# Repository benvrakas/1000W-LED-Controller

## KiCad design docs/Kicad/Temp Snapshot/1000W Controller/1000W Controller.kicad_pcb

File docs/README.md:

# 1000W LED Projector Controller Firmware (v2.0)

Firmware for a high-power (1000W) LED projector controller based on the **Adafruit Feather M4 CAN Express (SAME51)**. It manages a **Mean Well UHP-1500-48** power supply via CAN Bus, controls active liquid cooling, and provides a user interface via a Button, OLED, and Rotary Encoder.

## 1. System Overview
This system manages the power and cooling of a high-power COB LED array. It ensures safe operation through rigorous state management, PI-based thermal monitoring, and active fault protection.

### Key Features
*   **Power Control**: Digital control of **Mean Well UHP-1500-48** PSU via Native CAN Bus (PMBus protocol). Includes programmable output voltage (50~120%) and constant current limits (20~100%).
*   **Active Cooling**: PI (Proportional-Integral) controllers dynamically adjust Radiator Fans, Pump, and Aux Fans to strictly maintain target temperatures.
*   **User Interface**: OLED status display (128x32) and Rotary Encoder input for brightness mapping.
*   **Safety**:
    *   Latched `ERROR_KILL` state for critical faults (Over-temp, Pump failure, CAN timeout).
    *   Hardware enable lines dropped immediately on fault.

## 2. Hardware Components
The system manages the following specific high-performance components:
*   **Microcontroller:** Adafruit Feather M4 CAN Express (SAME51J19A).
*   **LED Array:** **Getian High-Density COB LED**. These specialized emitters produce intense localized heat and require precise power limits (up to 22.0A) and strict thermal management to prevent lumen degradation.
*   **Power Supply:** **Mean Well UHP-1500-48**. A 1500W, 48V industrial power supply. It is controlled via the PMBus protocol over the native CAN bus, allowing the microcontroller to set exact current limits and slew rates digitally.
*   **Cooling System (Liquid Loop):**
    *   **Water Pump:** **Xylem/Laing Ecocirc D5 Vario**. A highly reliable, shaftless spherical motor pump controlled via PWM with tachometer feedback.
    *   **Radiator Fans:** High static pressure 120mm PWM fans (e.g., NMB Technologies 12038VA series) to force air through the liquid cooling radiator.
    *   **Auxiliary/Lens Fans:** Additional PWM fans (e.g., Delta FFB series) to cool the optical path and projector lenses.
*   **Sensors:** Two 10k NTC Thermistors (Beta: 3950) for monitoring both the LED block temperature and the circulating Water temperature.

### 2.1 Pinout Mapping

## 3. Core Architectural Pattern
The software is structured using a **Dependency Injection (DI)** pattern, implemented in C++ with the Arduino/PlatformIO framework. This cleanly separates the hardware driver layer from the higher-level business logic.

### 3.1 Hardware Layer (`src/core/Hardware.cpp`)
*   **Role:** The "Composition Root". Instantiates all physical drivers (Tachometers, CAN backend, OLED, Thermistors) and pin configurations.
*   **Key Components:**
    *   `NativeCanBackend`: Adapts the SAMD51 hardware CAN controller to the `ICanBackend` interface.
    *   `TachometerManager`: Handles PWM output and tachometer pulse counting.

### 3.2 AppContext (`include/core/AppContext.h`)
*   **Role:** The "Toolbelt". A struct containing references to all hardware instances.
*   **Purpose:** Passed to the `SystemController` and Services, allowing them to access hardware without relying on global variables.

### 3.3 System Controller (`src/state/SystemController.cpp`)
*   **Role:** The "Brain". Manages the high-level Finite State Machine (FSM) and owns the domain services.
*   **States:**
    1.  **INIT**: Validates sensors, spins up pumps/fans, and checks for hardware faults before enabling high power.
    2.  **RUN**: The main control loop. Updates services, inputs, and UI.
    3.  **ERROR_KILL**: A latched safety state entered upon critical faults (Over-temp, CAN timeout). Disables PSU immediately.

## 4. Domain Services
Logic is divided into isolated services, injected with their specific dependencies.

| Service | Responsibility | Dependencies |
| :--- | :--- | :--- |
| **`PsuService`** | Manages LED current setpoint, slew limiting, and PSU enable/disable logic. | `CanBusManager` |
| **`CoolingService`** | Runs PI controllers to maintain target temperatures for the LED block and water loop. | `TachometerManager`, `ThermistorManager` |
| **`InputService`** | Processes encoder rotation and power button (arm/disarm) logic. | `EncoderManager`, `PowerButtonManager` |
| **`UiController`** | Renders the system state to the OLED display (Telemetry, Gauges, Errors). | `OledManager` |

## 5. Operational Flow & State Machine

### 5.1 Boot-Up and Initialization (`INIT` State)
When the system is plugged in, it enters the `INIT` state and begins a multi-step verification process to bootstrap the hardware:
1.  **Board Pins:** GPIOs are configured. Crucially, all PWM outputs and the `PSU_REMOTE` pin are forced `LOW` to ensure the system boots in a safe, unpowered state.
2.  **Cooling Priming:** The D5 pump and all fans are initialized and commanded to a minimum "deadstart" duty cycle to prime the liquid cooling loop, clear air bubbles, and establish baseline airflow. (Note: The `INIT` sequence primes the loop immediately without waiting for the fans/pump to physically spin up to avoid unnecessarily blocking the boot sequence. RPM is instead continuously monitored in the `RUN` state.)
3.  **PSU Init:** The Mean Well CAN interface is initialized, but the remote ON/OFF gate remains **disabled** (`LOW`).
4.  **Display:** The OLED boots and shows the startup screen.
5.  **Transition:** Once all steps pass, the system transitions into the `RUN` state. If any step times out (taking longer than 500ms), the system aborts to the `ERROR_KILL` state.

### 5.2 Normal Operation (`RUN` State)
In the `RUN` state, the main operational loop executes.

**Active PI Cooling Control:**
The `CoolingService` runs two separate Proportional-Integral (PI) controllers to maintain optimal temperatures:
*   **LED Loop (Fans):** Targets exactly **55.0°C** at the LED block. The PI controller dynamically adjusts the radiator and aux fans to find the exact equilibrium RPM needed to hold this temperature, protecting the Getian COB from thermal degradation.
*   **Water Loop (Pump):** Targets **40.0°C** for the circulating liquid. The pump's PI controller runs with softer tuning parameters to account for the high thermal mass of the liquid loop.
*   *Anti-Windup & Safety:* The integrators are capped to prevent windup, and are added on top of the "deadstart" minimum duties to ensure the fans and pump never stall during operation.

**Power Control & The Button:**
By default, even in the `RUN` state, the LED array is OFF and the PSU remote gate remains disabled. The virtual brightness knob is initialized at 0%. 
To power on the LED array, the user must **press and hold the power button for $\ge$ 3000ms**. 
*   **Arming:** Once held for 3 seconds, the system is marked as "Armed".
*   **Power On Sequence:** The `PsuService` sets the PSU Remote gate `HIGH` (physically enabling the Mean Well PSU) and sends a PMBus CAN command to enable output.
*   **Slew Rate Control:** The requested LED current smoothly ramps up to the target value (set by the encoder knob) at a controlled rate of **30% per second**. This prevents inrush currents and thermal shock to the LED array.
*   **Power Off Sequence:** Pressing the button again "Disarms" the system. The current setpoint slews down at a faster rate of **100% per second**. *Only when the applied current reaches $\le$ 1%* does the controller physically drop the `PSU_REMOTE` gate to `LOW` and disable CAN output. A hard timeout of 3000ms is enforced during this disarm phase: if CAN communication faults or hangs during this exact slew-down window, the firmware unconditionally drops the `PSU_REMOTE` gate to `LOW`, guaranteeing hardware shutoff.

### 5.3 Fault Protection (`ERROR_KILL` State)
Due to the extreme thermal output of a 1000W LED, safety is paramount. The system continuously polls for critical faults. If a fault is detected, the `FaultManager` immediately transitions the system into the latched `ERROR_KILL` state.

**Critical Cut-Offs:**
*   **LED Over-Temperature:** Triggers if LED thermistor reads **> 75.0°C**.
*   **Water Over-Temperature:** Triggers if the liquid cooling loop reaches **> 50.0°C**.
*   **Cooling Stalls:** Fans and pumps have tachometer feedback which is continuously polled in the `RUN` state. If a PWM duty is commanded but the RPM falls below the stall thresholds (whether the LED is armed or not), the system throws a precise `COOLING_FAILURE` fault:
    *   Radiator/PSU Fan Stall: **< 300 RPM**
    *   Auxiliary Fan Stall: **< 300 RPM**
    *   Pump Stall: **< 150 RPM**
*   **CAN Timeout:** If the PSU stops responding to CAN telemetry requests for **> 500ms**.

**When `ERROR_KILL` is triggered:**
1.  **Immediate Disconnect:** The `psu.setOperation(false)` command is fired, which drops the `PSU_REMOTE` gate to `LOW` (hardware disable) and sends a CAN disable command.
2.  **Latch:** The system halts all normal operations. It will not restart or accept input until physically unplugged and reset.

## 6. Directory Structure
*   `src/` - Implementation files.
    *   `core/` - Hardware instantiation (`Hardware.cpp`) and dependency injection (`AppContext`).
    *   `services/` - Business logic (`CoolingService`, `PsuService`).
    *   `drivers/` - Hardware abstraction (`NativeCanBackend`, `OLED`).
    *   `state/` - Finite State Machine (`Init`, `Run`, `Error`).
*   `include/config/` - System configuration.
    *   `PinMap.h` - Hardware pin definitions (PWM, Tach, I2C, etc. CAN uses internal board pins).
    *   `ThermalConfig.h` - Thermistor beta values, Fan/Pump RPM limits, and **PI Controller Configuration** (Target temps, Kp, Ki).
    *   `PowerConfig.h` - PSU voltage/current limits, CAN bus bitrate, and Slew rates.
*   `docs/` - Documentation.

## 7. Protocols
*   **CAN Bus**: Uses 29-bit Extended IDs.
    *   **Current Control**: Uses PMBus Linear11 encoding. 100% LED Power (22A) is scaled relative to the PSU Max (31.3A) to ensure correct current command.

## 8. Building & Flashing
This project uses **PlatformIO**.

**Note for AI Agents / CLI Users:**
If `pio` is not in your PATH, use the full path: `C:\Users\benvr\.platformio\penv\Scripts\pio.exe` (or add it to your PATH).

1.  **Build**: `pio run`
2.  **Upload**: `pio run -t upload`
3.  **Monitor**: `pio device monitor`

## License
Proprietary / Internal Use.

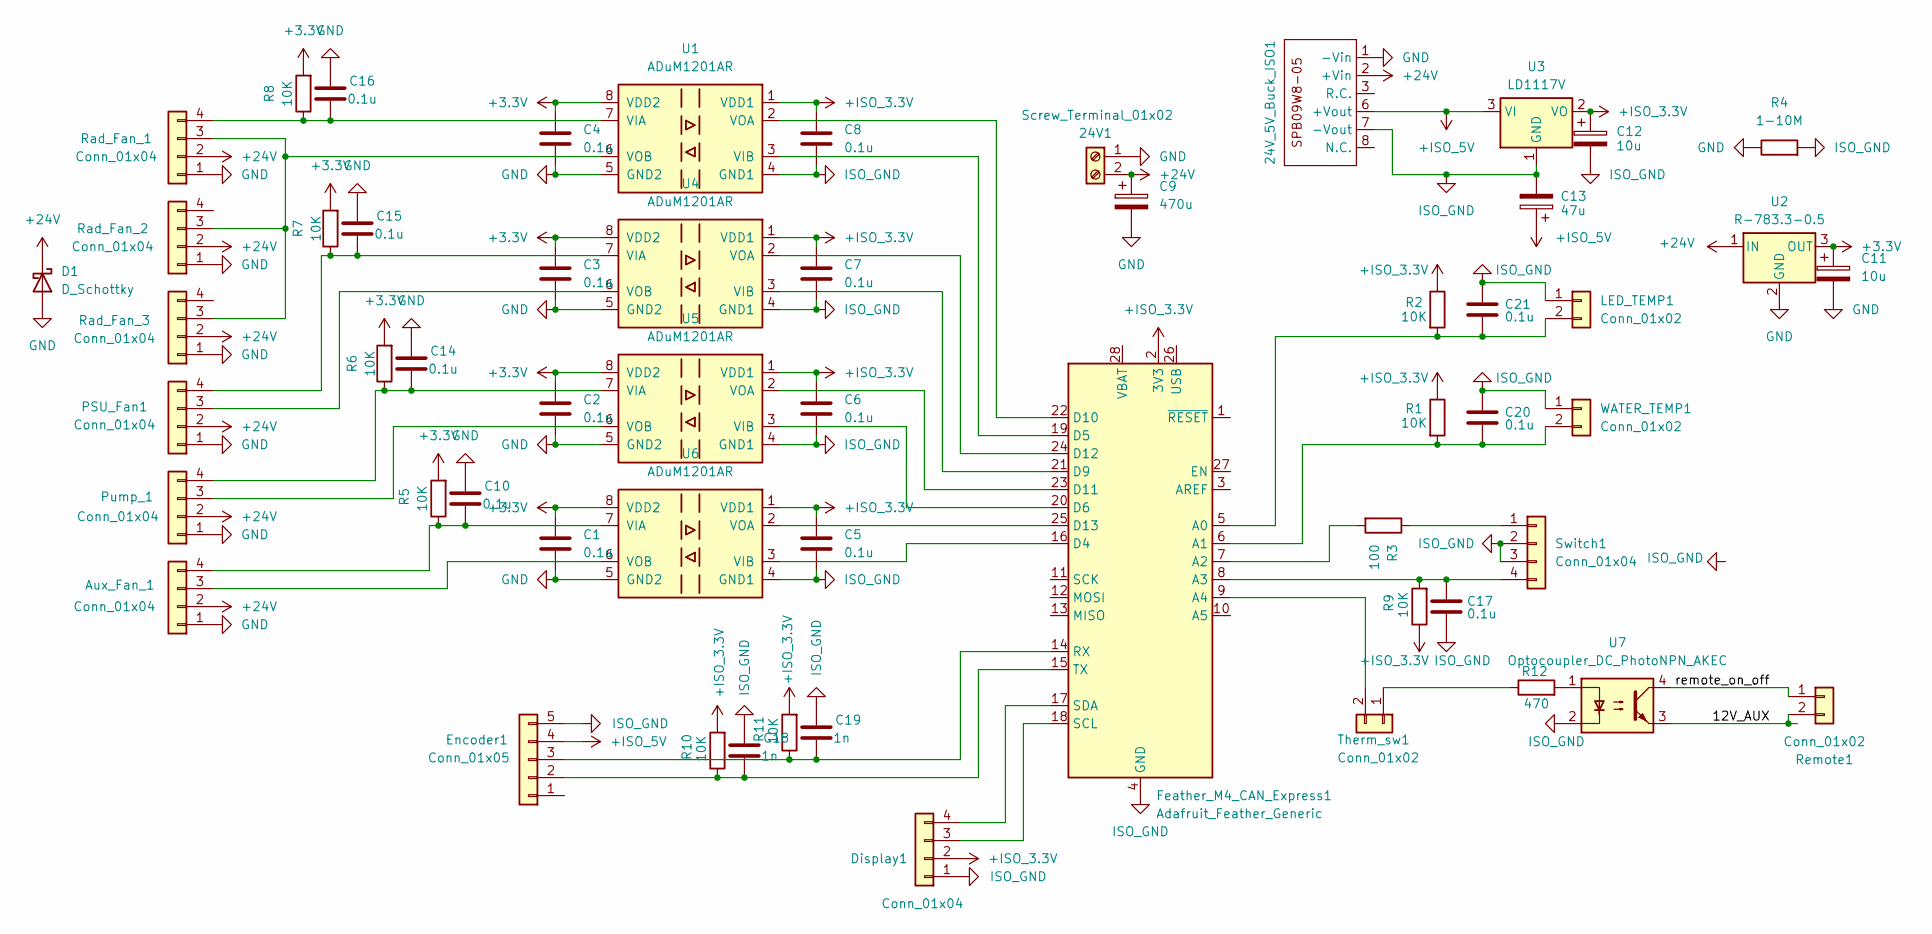
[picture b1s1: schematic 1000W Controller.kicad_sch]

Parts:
24V1: Screw_Terminal_01x02; TerminalBlock_Phoenix_MKDS-1,5-2-5.08_1x02_P5.08mm_Horizont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
24V_5V_Buck_ISO1: SPB09W8-05
Aux_Fan_1: Conn_01x04; Molex_KK-254_AE-6410-04A_1x04_P2.54mm_Vertical
C1, C2, C3, C4, C5, C6, C7, C8, C10, C14, C15, C16, C17, C20, C21: 0.1u; C_0805_2012Metric
C9: 470u; CP_Radial_D10.0mm_P5.00mm
C11, C12: 10u; C_0805_2012Metric
C13: 47u; C_1210_3225Metric
C18, C19: 1n; C_0805_2012Metric
D1: D_Schottky; D_DO-201AD_P15.24mm_Horizontal
Display1: Conn_01x04; JST_XH_B4B-XH-A_1x04_P2.50mm_Vertical
Encoder1: Conn_01x05; JST_XH_B5B-XH-A_1x05_P2.50mm_Vertical
Feather_M4_CAN_Express1: Adafruit_Feather_Generic; Adafruit_Feather
LED_TEMP1: Conn_01x02; JST_XH_B2B-XH-A_1x02_P2.50mm_Vertical
PSU_Fan1: Conn_01x04; Molex_KK-254_AE-6410-04A_1x04_P2.54mm_Vertical
Pump_1: Conn_01x04; Molex_KK-254_AE-6410-04A_1x04_P2.54mm_Vertical
R1, R2, R5, R6, R7, R8, R9, R10, R11: 10K; R_0805_2012Metric
R3: 100; R_0805_2012Metric
R4: 1-10M; R_0805_2012Metric
R12: 470; R_0805_2012Metric
Rad_Fan_1, Rad_Fan_2, Rad_Fan_3: Conn_01x04; Molex_KK-254_AE-6410-04A_1x04_P2.54mm_Vertical
Remote1: Conn_01x02; JST_XH_B2B-XH-A_1x02_P2.50mm_Vertical
Switch1: Conn_01x04; JST_XH_B4B-XH-A_1x04_P2.50mm_Vertical
Therm_sw1: Conn_01x02; JST_XH_B2B-XH-A_1x02_P2.50mm_Vertical
U1, U4, U5, U6: ADuM1201AR; SOIC-8_3.9x4.9mm_P1.27mm
U2: R-783.3-0.5; Converter_DCDC_RECOM_R-78E-0.5_THT
U3: LD1117V; TO-220-3_Vertical
U7: Optocoupler_DC_PhotoNPN_AKEC; DIP-4_W7.62mm
WATER_TEMP1: Conn_01x02; JST_XH_B2B-XH-A_1x02_P2.50mm_Vertical

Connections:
+3.3V: C1.1, C2.1, C3.1, C4.1, C11.1, R5.2, R6.2, R7.2, R8.2, U1.8 (VDD2), U2.3 (OUT), U4.8 (VDD2), U5.8 (VDD2), U6.8 (VDD2)
+24V: 24V1.2, 24V_5V_Buck_ISO1.2 (+Vin), Aux_Fan_1.2, C9.1, D1.1 (K), PSU_Fan1.2, Pump_1.2, Rad_Fan_1.2, Rad_Fan_2.2, Rad_Fan_3.2, U2.1 (IN)
+ISO_3.3V: C5.1, C6.1, C7.1, C8.1, C12.1, Display1.2, Feather_M4_CAN_Express1.2 (3V3), R1.1, R2.1, R9.1, R10.2, R11.2, U1.1 (VDD1), U3.2 (VO), U4.1 (VDD1), U5.1 (VDD1), U6.1 (VDD1)
+ISO_5V: 24V_5V_Buck_ISO1.6 (+Vout), C13.1, Encoder1.4, U3.3 (VI)
/12V_AUX: Remote1.2, U7.3
/remote_on_off: Remote1.1, U7.4
GND: 24V1.1, 24V_5V_Buck_ISO1.1 (-Vin), Aux_Fan_1.1, C1.2, C2.2, C3.2, C4.2, C9.2, C10.1, C11.2, C14.1, C15.1, C16.1, D1.2 (A), PSU_Fan1.1, Pump_1.1, R4.1, Rad_Fan_1.1, Rad_Fan_2.1, Rad_Fan_3.1, U1.5 (GND2), U2.2 (GND), U4.5 (GND2), U5.5 (GND2), U6.5 (GND2)
ISO_GND: 24V_5V_Buck_ISO1.7 (-Vout), C5.2, C6.2, C7.2, C8.2, C12.2, C13.2, C17.2, C18.1, C19.1, C20.1, C21.1, Display1.1, Encoder1.5, Feather_M4_CAN_Express1.4 (GND), LED_TEMP1.1, R4.2, Switch1.2, Switch1.3, U1.4 (GND1), U3.1 (GND), U4.4 (GND1), U5.4 (GND1), U6.4 (GND1), U7.2, WATER_TEMP1.1
unnamed: Aux_Fan_1.3, U6.6 (VOB)
unnamed: Aux_Fan_1.4, C10.2, R5.1, U6.7 (VIA)
unnamed: Display1.3, Feather_M4_CAN_Express1.18 (SCL)
unnamed: Display1.4, Feather_M4_CAN_Express1.17 (SDA)
unnamed: C18.2, Encoder1.2, Feather_M4_CAN_Express1.15 (TX), R10.1
unnamed: C19.2, Encoder1.3, Feather_M4_CAN_Express1.14 (RX), R11.1
unnamed: C21.2, Feather_M4_CAN_Express1.5 (A0), LED_TEMP1.2, R2.2
unnamed: C20.2, Feather_M4_CAN_Express1.6 (A1), R1.2, WATER_TEMP1.2
unnamed: Feather_M4_CAN_Express1.7 (A2), R3.2
unnamed: C17.1, Feather_M4_CAN_Express1.8 (A3), R9.2, Switch1.4
unnamed: Feather_M4_CAN_Express1.9 (A4), Therm_sw1.2
unnamed: Feather_M4_CAN_Express1.16 (D4), U6.3 (VIB)
unnamed: Feather_M4_CAN_Express1.19 (D5), U1.3 (VIB)
unnamed: Feather_M4_CAN_Express1.20 (D6), U5.3 (VIB)
unnamed: Feather_M4_CAN_Express1.21 (D9), U4.3 (VIB)
unnamed: Feather_M4_CAN_Express1.22 (D10), U1.2 (VOA)
unnamed: Feather_M4_CAN_Express1.23 (D11), U5.2 (VOA)
unnamed: Feather_M4_CAN_Express1.24 (D12), U4.2 (VOA)
unnamed: Feather_M4_CAN_Express1.25 (D13), U6.2 (VOA)
unnamed: PSU_Fan1.3, U4.6 (VOB)
unnamed: C15.2, PSU_Fan1.4, R7.1, U4.7 (VIA)
unnamed: Pump_1.3, U5.6 (VOB)
unnamed: C14.2, Pump_1.4, R6.1, U5.7 (VIA)
unnamed: R12.2, U7.1
unnamed: Rad_Fan_1.3, Rad_Fan_2.3, Rad_Fan_3.3, U1.6 (VOB)
unnamed: C16.2, R8.1, Rad_Fan_1.4, U1.7 (VIA)
unnamed: R3.1, Switch1.1
unnamed: R12.1, Therm_sw1.1

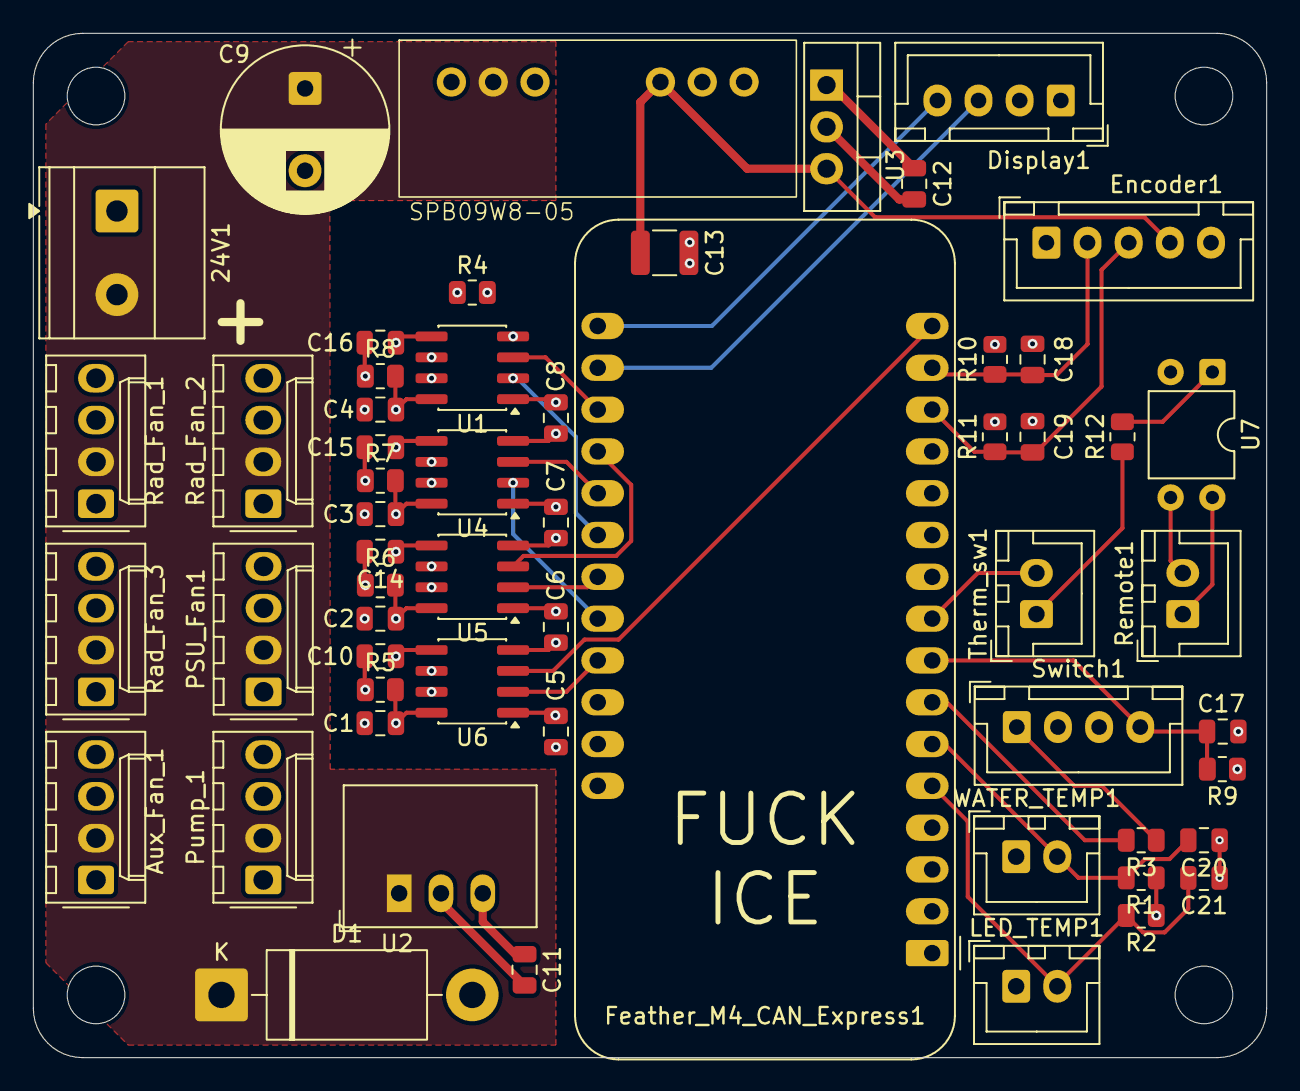
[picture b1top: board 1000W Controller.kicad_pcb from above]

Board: 4 copper layers, 74.9 x 62.2 mm, 57 parts (0 on the bottom side), 36 nets.

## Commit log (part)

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2026-01-01 Initial Commit: 1000W LED Projector Controller
2026-01-22 Initial commit: Monorepo with ProjectorMaster, ProjectorSandbox, and SystemShared lib
2026-01-23 Clean up file system and finalize library links
2026-01-23 Consolidate gitignore to root
2026-01-25 Device drivers update
2026-01-27 My branch for the project, which includes updates to the tachometer functionality
2026-02-10 Update for Shop Day
2026-02-10 Github is buns sometimes
2026-02-10 update latest changes from bauer branch
2026-02-11 Revert "update latest changes from bauer branch"
    This reverts commit 800e55d7c698ee660c3ee905f890c6a98ca8f10c.
2026-02-20 Mostly Power Button Code Changes
2026-02-20 Fixed Linker Errors
2026-02-20 Press alt f4 to kiss your dad
2026-03-02 Vibe coding time
2026-03-02 OPSU4.5
2026-03-02 Good Night
2026-03-02 Gemini
2026-03-02 Final upload before classes. GLHF
2026-03-02 union destroyed
2026-03-03 Consolidated headers
2026-03-03 Removed sandbox
2026-03-10 Documentation
2026-03-10 im him
2026-03-22 Error LED
2026-03-22 bugs
